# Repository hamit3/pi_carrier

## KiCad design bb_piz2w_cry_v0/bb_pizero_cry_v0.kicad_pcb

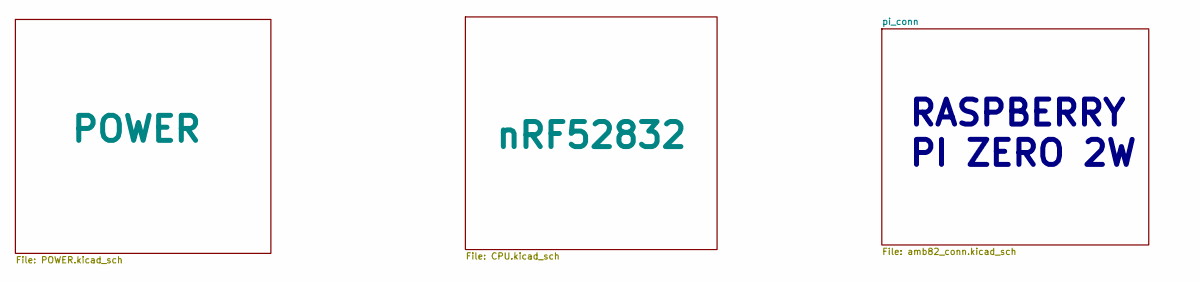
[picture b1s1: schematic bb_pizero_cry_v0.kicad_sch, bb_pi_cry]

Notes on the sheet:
RASPBERRY PI ZERO 2W

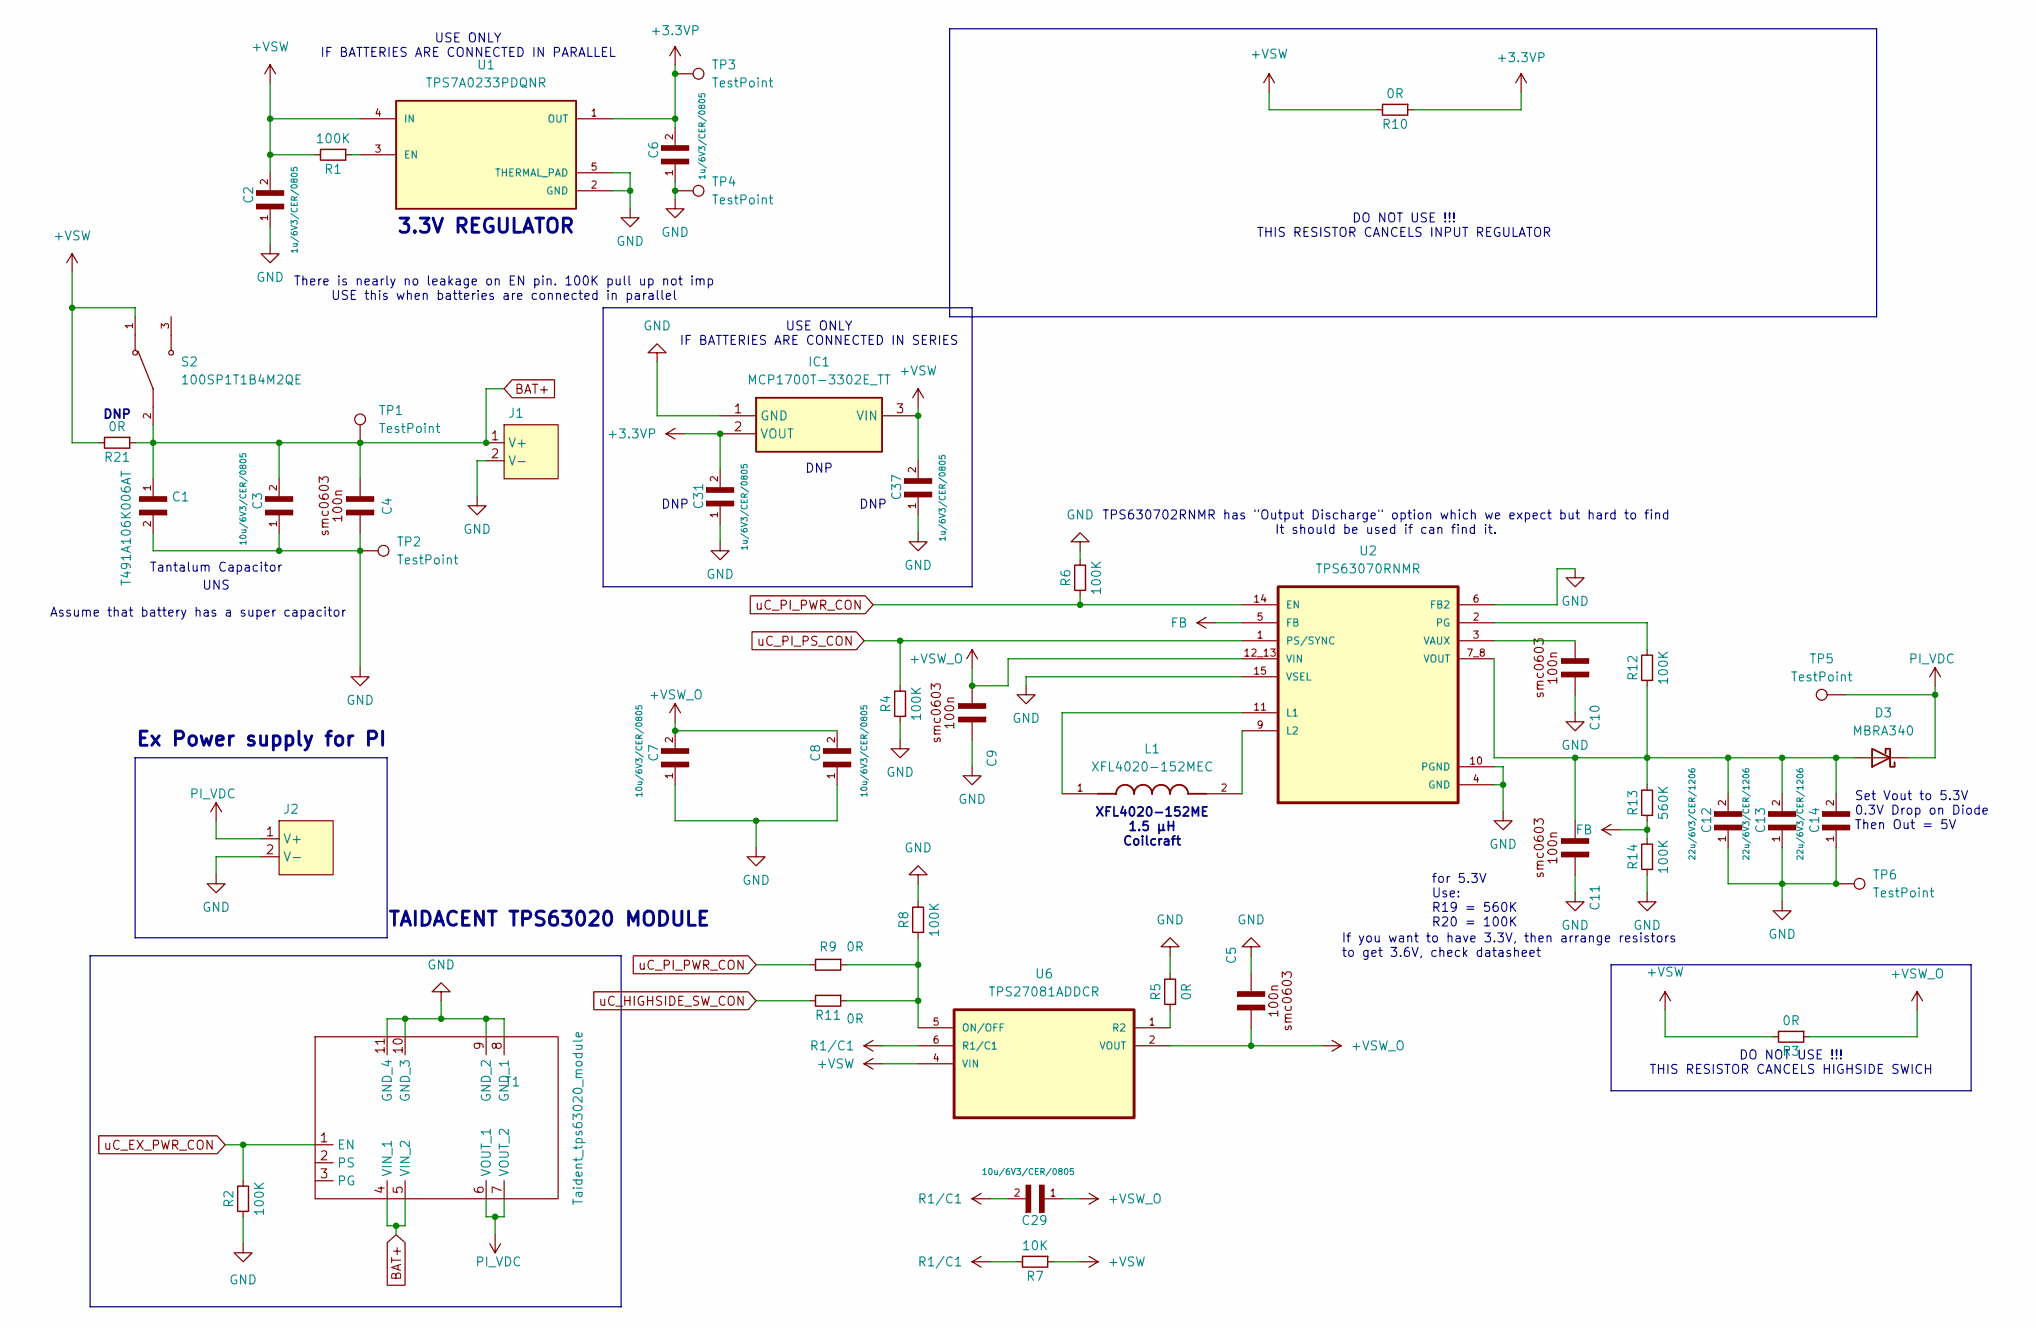
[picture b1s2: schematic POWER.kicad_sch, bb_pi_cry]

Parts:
C1: T491A106K006AT; CAPC3216X110N
C2, C6, C31, C37: 1u/6V3/CER/0805; CAPC2012X140N
C3, C7, C8, C29: 10u/6V3/CER/0805; CAPC2012X140N
C4, C5, C9, C10, C11: 100n; CAP_CL10_SAM
C12, C13, C14: 22u/6V3/CER/1206; C_1206_3216Metric_Pad1.33x1.80mm_HandSolder
D3: MBRA340; D_SMA; Part Number MBRA340T3GOSDKR-ND
IC1: MCP1700T-3302E_TT; SOT95P237X112-3N; Manufacturer_Part_Number MCP1700T-3302E/TT; Mouser Part Number 579-MCP1700T3302E/TT
J1: JST_PH_S2B-PH-K_1x02_P2.00mm_Horizontal
J2: JST_XH_B2B-XH-AM_1x02_P2.50mm_Vertical
L1: XFL4020-152MEC; IND_XFL4020-152MEC; PARTREV 11/02/18
R1, R4, R6, R8, R12, R14: 100K; RESC1508X55N
R2: 100K; R_1206_3216Metric_Pad1.30x1.75mm_HandSolder
R3, R10, R21: 0R; R_1206_3216Metric_Pad1.30x1.75mm_HandSolder
R5, R9, R11: 0R; RESC1508X55N
R7: 10K; RESC1508X55N
R13: 560K; RESC1508X55N
S2: 100SP1T1B4M2QE; SW_100SP1T1B4M2QE; PARTREV E
T1: Taident_tps63020_module; Taidacent_tps63020
TP1, TP2, TP3, TP4, TP5, TP6: TestPoint; TestPoint_Pad_2.0x2.0mm
U1: TPS7A0233PDQNR; SOT95P280X145-5N; PARTREV C
U2: TPS63070RNMR; VREG_TPS63070RNMR
U6: TPS27081ADDCR; SOT95P280X110-6N

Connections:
+3.3VP: C6.2, C31.2, IC1.2 (VOUT), R10.1, TP3.1, U1.1 (OUT); also elsewhere on the board
+VSW: C2.2, C37.2, IC1.3 (VIN), R1.2, R3.2, R7.1, R10.2, R21.2, S2.1, U1.4 (IN), U6.4 (VIN)
+VSW_O: C5.2, C7.2, C8.2, C9.2, C29.1, R3.1, U2.12_13 (VIN), U6.2 (VOUT), U6.3 (VOUT)
BAT+: C1.1, C3.2, C4.2, J1.1 (V+), R21.1, S2.2, T1.4 (VIN_1), T1.5 (VIN_2), TP1.1
FB: R13.1, R14.2, U2.5 (FB)
GND: C1.2, C2.1, C3.1, C4.1, C5.1, C6.1, C7.1, C8.1, C9.1, C10.1, C11.1, C12.1, C13.1, C14.1, C31.1, C37.1, IC1.1 (GND), J1.2 (V-), J2.2 (V-), R2.1, R4.1, R5.2, R6.2, R8.2, R14.1, T1.8 (GND_1), T1.9 (GND_2), T1.10 (GND_3), T1.11 (GND_4), TP2.1, TP4.1, TP6.1, U1.2 (GND), U1.5 (THERMAL_PAD), U2.4 (GND), U2.6 (FB2), U2.10 (PGND), U2.15 (VSEL); also elsewhere on the board
unnamed: C11.2, C12.2, C13.2, C14.2, D3.2 (A), R12.1, R13.2, U2.7_8 (VOUT)
unnamed: R1.1, U1.3 (EN)
unnamed: L1.1, U2.11 (L1)
unnamed: L1.2, U2.9 (L2)
unnamed: R12.2, U2.2 (PG)
unnamed: C10.2, U2.3 (VAUX)
unnamed: R8.1, R9.1, R11.1, U6.5 (ON/OFF)
unnamed: R5.1, U6.1 (R2)
PI_VDC: D3.1 (K), J2.1 (V+), T1.6 (VOUT_1), T1.7 (VOUT_2), TP5.1; also elsewhere on the board
R1/C1: C29.2, R7.2, U6.6 (R1/C1)
uC_EX_PWR_CON: R2.2, T1.1 (EN); also elsewhere on the board
uC_HIGHSIDE_SW_CON: R11.2; also elsewhere on the board
uC_PI_PS_CON: R4.2, U2.1 (PS/SYNC); also elsewhere on the board
uC_PI_PWR_CON: R6.1, R9.2, U2.14 (EN); also elsewhere on the board

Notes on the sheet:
TAIDACENT TPS63020 MODULE
UNS
Set Vout to 5.3V 0.3V Drop on Diode Then Out = 5V
DO NOT USE !!! THIS RESISTOR CANCELS INPUT REGULATOR
USE ONLY IF BATTERIES ARE CONNECTED IN SERIES
for 5.3V Use: R19 = 560K R20 = 100K
DNP
3.3V REGULATOR
Assume that battery has a super capacitor
There is nearly no leakage on EN pin. 100K pull up not imp USE this when batteries are connected in parallel
XFL4020-152ME 1.5 µH Coilcraft
USE ONLY IF BATTERIES ARE CONNECTED IN PARALLEL
DO NOT USE !!! THIS RESISTOR CANCELS HIGHSIDE SWICH
Tantalum Capacitor
TPS630702RNMR has "Output Discharge" option which we expect but hard to find It should be used if can find it.
Ex Power supply for PI
If you want to have 3.3V, then arrange resistors to get 3.6V, check datasheet

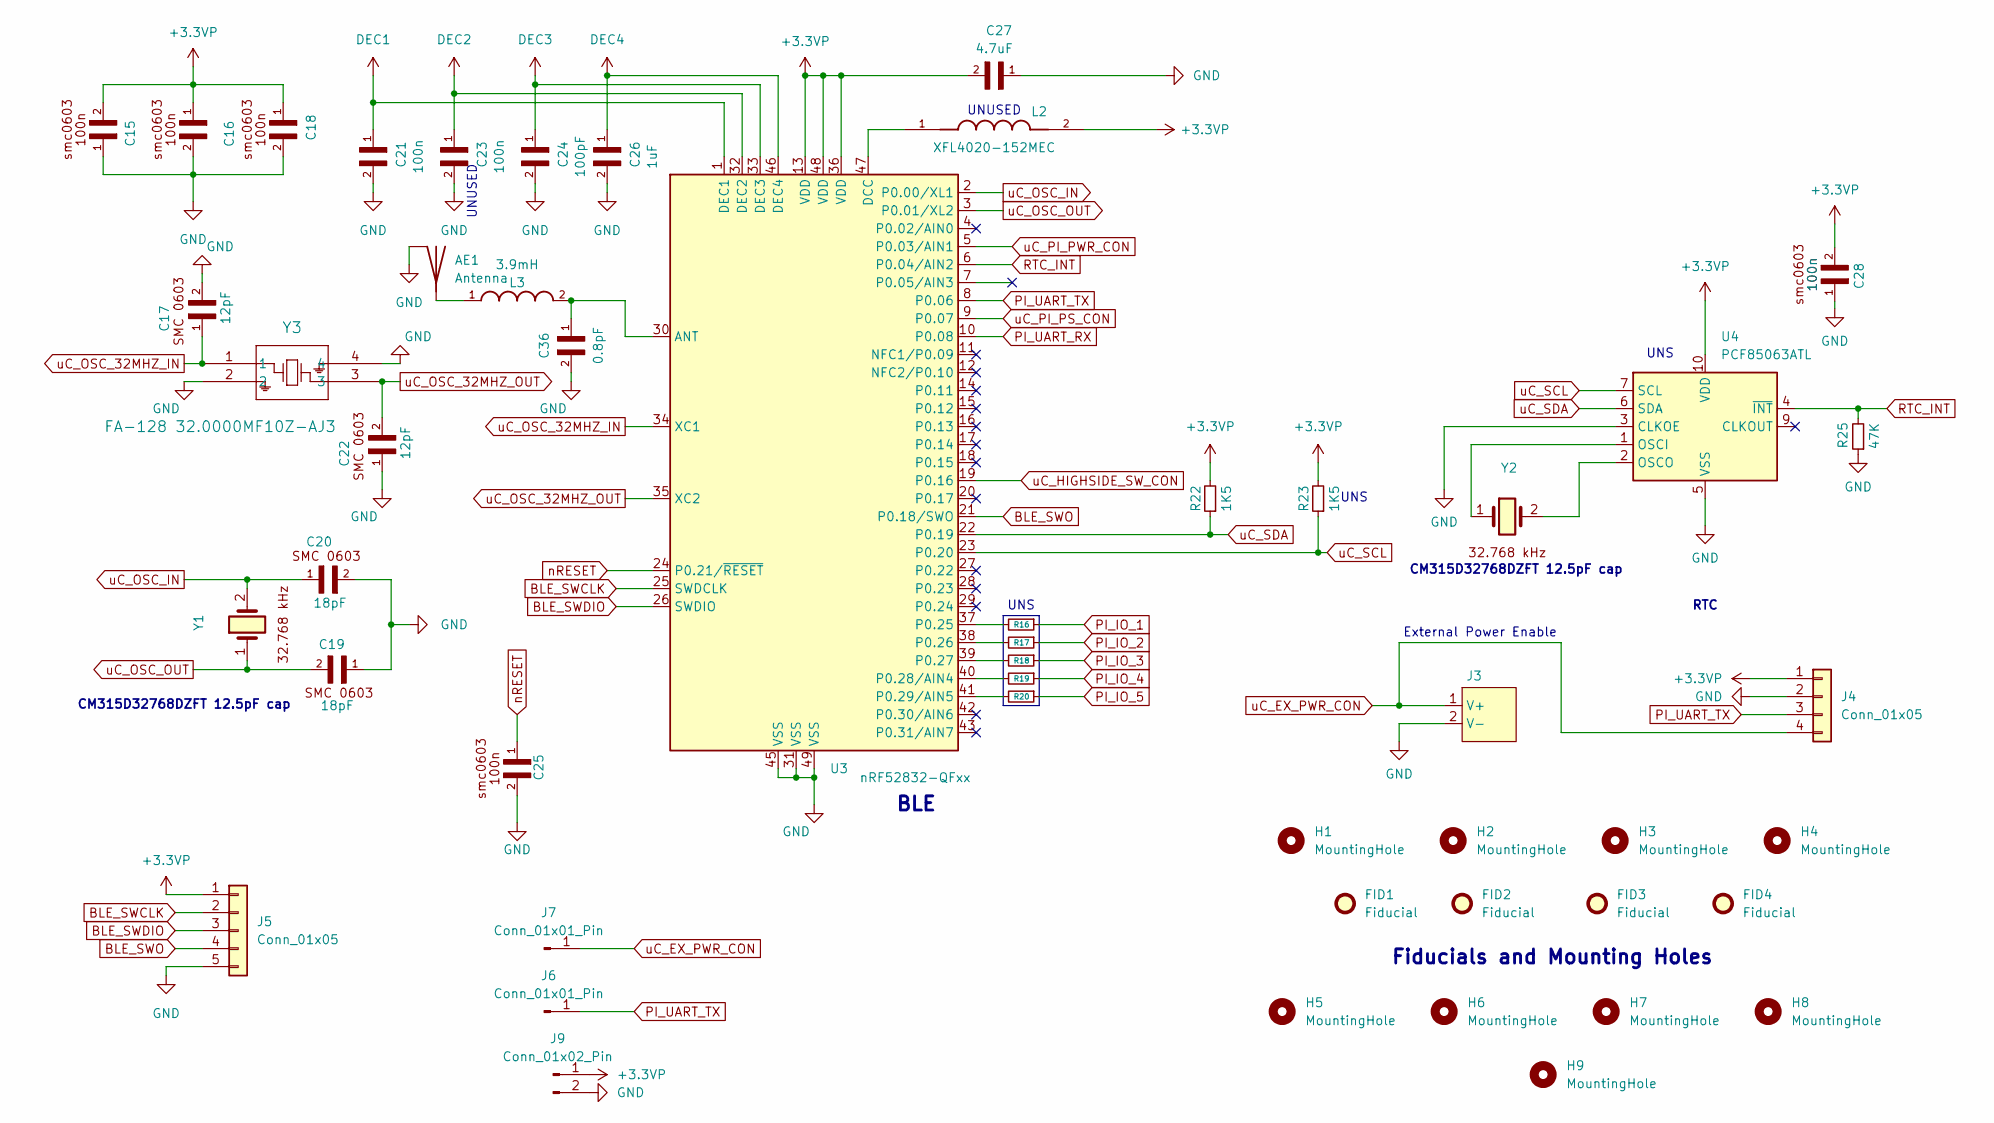
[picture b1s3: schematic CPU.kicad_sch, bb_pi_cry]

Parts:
AE1: Antenna; Texas_SWRA117D_2.4GHz_Right
C15, C16, C18, C21, C23, C25, C28: 100n; CAP_CL10_SAM
C17, C22: 12pF; CAPC1608X90N
C19, C20: 18pF; CAPC1608X90N
C24: 100pF; CAP_CL10_SAM
C26: 1uF; CAP_CL10_SAM
C27: 4.7uF; C_0201_0603Metric_Pad0.64x0.40mm_HandSolder
C36: 0.8pF; CAPC1005X55N
FID1, FID2, FID3, FID4: Fiducial; Fiducial_0.75mm_Mask2.25mm
H1, H2, H3, H4, H5, H6, H7, H8, H9: MountingHole; MountingHole_2.2mm_M2
J3: JST_XH_B2B-XH-AM_1x02_P2.50mm_Vertical
J4: Conn_01x05; PinHeader_1x04_P2.54mm_Vertical
J5: Conn_01x05; PinHeader_1x05_P2.54mm_Vertical
J6, J7: Conn_01x01_Pin; PinHeader_1x01_P2.54mm_Vertical
J9: Conn_01x02_Pin; PinHeader_1x02_P2.54mm_Vertical
L2: XFL4020-152MEC; IND_XFL4020-152MEC; PARTREV 11/02/18
L3: 3.9mH; INDC1005X55N
R16, R17, R18, R19, R20: 0R; RESC1508X55N
R22, R23: 1K5; RESC1508X55N
R25: 47K; RESC1508X55N
U3: nRF52832-QFxx; QFN-48-1EP_6x6mm_P0.4mm_EP4.6x4.6mm
U4: PCF85063ATL; DFN-10-1EP_2.6x2.6mm_P0.5mm_EP1.3x2.2mm
Y1, Y2: XTAL_CM315D32768DZFT
Y3: FA-128 32.0000MF10Z-AJ3; FA-128_EPS

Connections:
+3.3VP: C15.2, C16.1, C18.1, C27.2, C28.2, J4.1, J5.1, J9.1, L2.2, R22.2, R23.2, U3.13 (VDD), U3.36 (VDD), U3.48 (VDD), U4.10 (VDD); also elsewhere on the board
BLE_SWCLK: J5.2, U3.25 (SWDCLK)
BLE_SWDIO: J5.3, U3.26 (SWDIO)
BLE_SWO: J5.4, U3.21 (P0.18/SWO)
DEC1: C21.1, U3.1 (DEC1)
DEC2: C23.1, U3.32 (DEC2)
DEC3: C24.1, U3.33 (DEC3)
DEC4: C26.1, U3.46 (DEC4)
GND: AE1.2 (GND_Ref), C15.1, C16.2, C17.2, C18.2, C19.1, C20.2, C21.2, C22.1, C23.2, C24.2, C25.2, C26.2, C27.1, C28.1, C36.2, J3.2 (V-), J4.2, J5.5, J9.2, R25.1, U3.31 (VSS), U3.45 (VSS), U3.49 (VSS), U4.3 (CLKOE), U4.5 (VSS), Y3.2, Y3.4; also elsewhere on the board
unnamed: AE1.1 (A), L3.1
unnamed: C36.1, L3.2, U3.30 (ANT)
unnamed: L2.1, U3.47 (DCC)
unnamed: R16.2, U3.37 (P0.25)
unnamed: R17.2, U3.38 (P0.26)
unnamed: R18.2, U3.39 (P0.27)
unnamed: R19.2, U3.40 (P0.28/AIN4)
unnamed: R20.2, U3.41 (P0.29/AIN5)
unnamed: U4.1 (OSCI), Y2.1
unnamed: U4.2 (OSCO), Y2.2
PI_IO_1: R16.1; also elsewhere on the board
PI_IO_2: R17.1; also elsewhere on the board
PI_IO_3: R18.1; also elsewhere on the board
PI_IO_4: R19.1; also elsewhere on the board
PI_IO_5: R20.1; also elsewhere on the board
PI_UART_RX: U3.10 (P0.08); also elsewhere on the board
PI_UART_TX: J4.3, J6.1, U3.8 (P0.06); also elsewhere on the board
RTC_INT: R25.2, U3.6 (P0.04/AIN2), U4.4 (~INT)
nRESET: C25.1, U3.24 (P0.21/~RESET)
uC_EX_PWR_CON: J3.1 (V+), J4.4, J7.1; also elsewhere on the board
uC_HIGHSIDE_SW_CON: U3.19 (P0.16); also elsewhere on the board
uC_OSC_32MHZ_IN: C17.1, U3.34 (XC1), Y3.1
uC_OSC_32MHZ_OUT: C22.2, U3.35 (XC2), Y3.3
uC_OSC_IN: C20.1, U3.2 (P0.00/XL1), Y1.2
uC_OSC_OUT: C19.2, U3.3 (P0.01/XL2), Y1.1
uC_PI_PS_CON: U3.9 (P0.07); also elsewhere on the board
uC_PI_PWR_CON: U3.5 (P0.03/AIN1); also elsewhere on the board
uC_SCL: R23.1, U3.23 (P0.20), U4.7 (SCL)
uC_SDA: R22.1, U3.22 (P0.19), U4.6 (SDA)

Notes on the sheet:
RTC
UNS
UNUSED
CM315D32768DZFT 12.5pF cap
Fiducials and Mounting Holes
BLE
External Power Enable

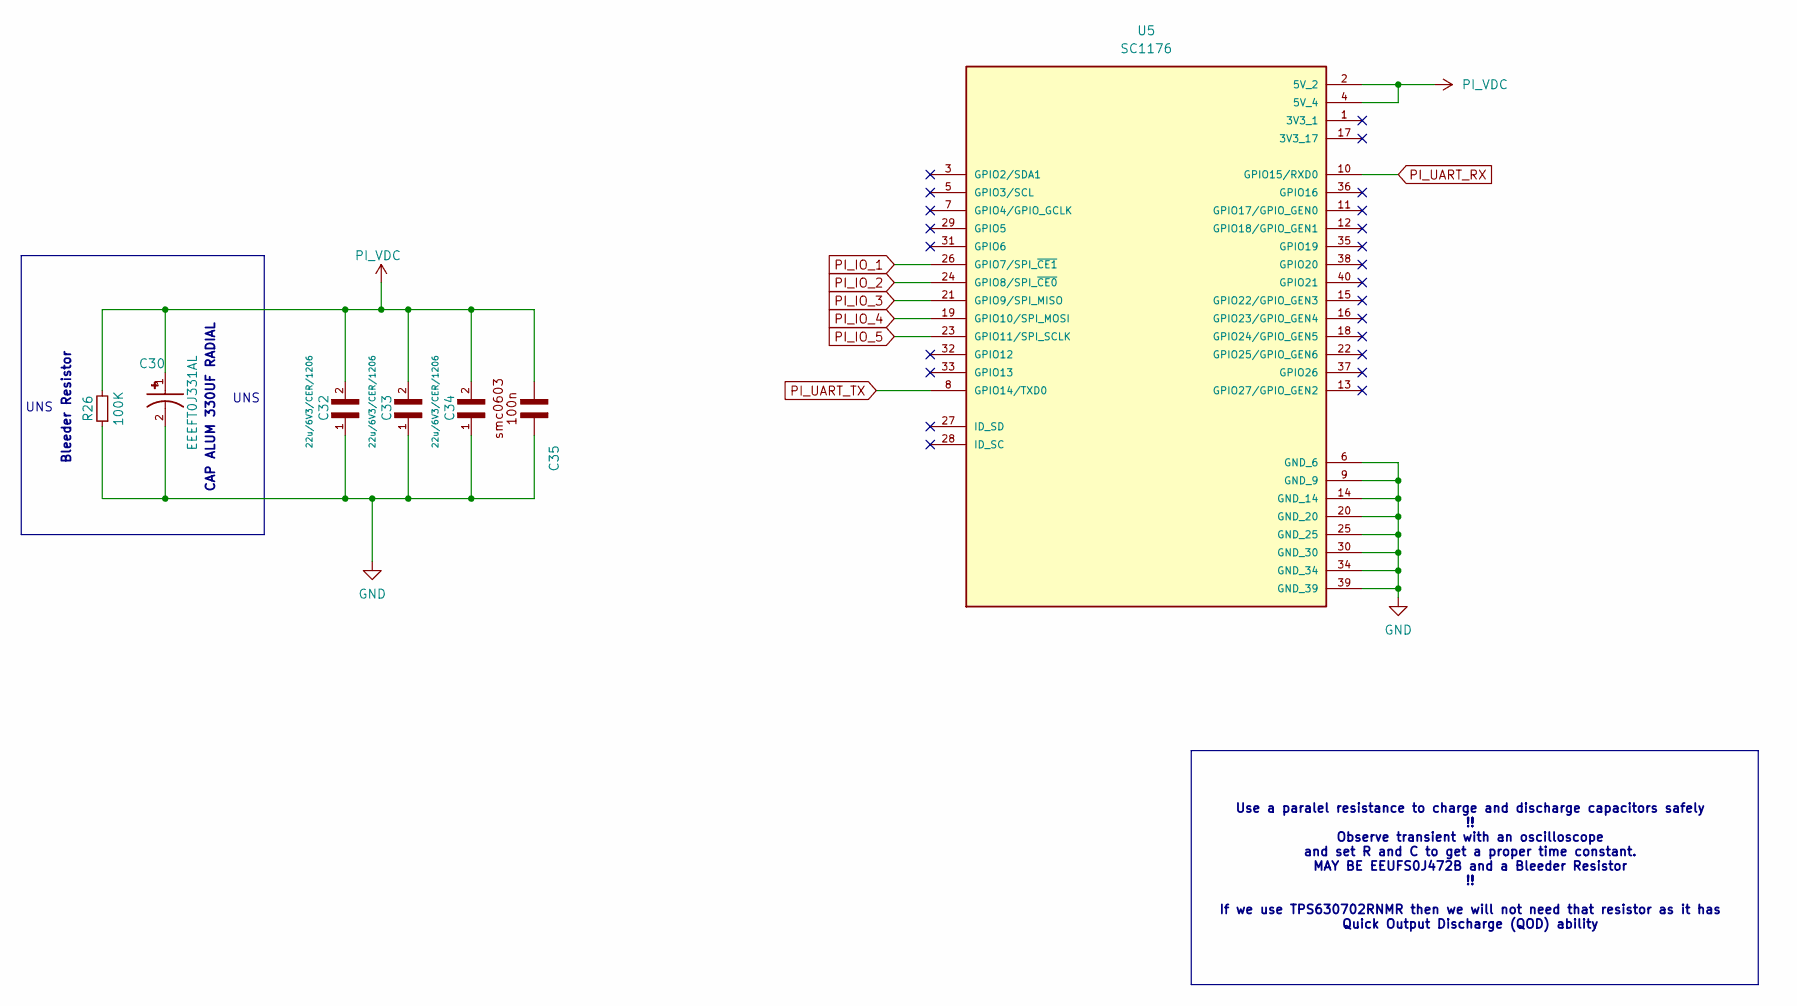
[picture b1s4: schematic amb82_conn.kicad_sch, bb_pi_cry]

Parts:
C30: EEEFT0J331AL; CAP_EEEFT0J331AL; PARTREV 10-Oct-19
C32, C33, C34: 22u/6V3/CER/1206; C_1206_3216Metric_Pad1.33x1.80mm_HandSolder
C35: 100n; CAP_CL10_SAM
R26: 100K; R_1206_3216Metric_Pad1.30x1.75mm_HandSolder
U5: SC1176; Raspberry_Pi_Zero_Socketed_THT_FaceDown_MountingHoles; PARTREV April 2024

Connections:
GND: C30.2, C32.1, C33.1, C34.1, C35.1, R26.1, U5.6 (GND_6), U5.9 (GND_9), U5.14 (GND_14), U5.20 (GND_20), U5.25 (GND_25), U5.30 (GND_30), U5.34 (GND_34), U5.39 (GND_39); also elsewhere on the board
PI_IO_1: U5.26 (GPIO7/SPI_~CE1); also elsewhere on the board
PI_IO_2: U5.24 (GPIO8/SPI_~CE0); also elsewhere on the board
PI_IO_3: U5.21 (GPIO9/SPI_MISO); also elsewhere on the board
PI_IO_4: U5.19 (GPIO10/SPI_MOSI); also elsewhere on the board
PI_IO_5: U5.23 (GPIO11/SPI_SCLK); also elsewhere on the board
PI_UART_RX: U5.10 (GPIO15/RXD0); also elsewhere on the board
PI_UART_TX: U5.8 (GPIO14/TXD0); also elsewhere on the board
PI_VDC: C30.1, C32.2, C33.2, C34.2, C35.2, R26.2, U5.2 (5V_2), U5.4 (5V_4); also elsewhere on the board

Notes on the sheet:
CAP ALUM 330UF RADIAL
Use a paralel resistance to charge and discharge capacitors safely !! Observe transient with an oscilloscope and set R and C to get a proper time constant. MAY BE EEUFS0J472B and a Bleeder Resistor !! If we use TPS630702RNMR then we will not need that resistor as it has Quick Output Discharge (QOD)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
UNS
Bleeder Resistor

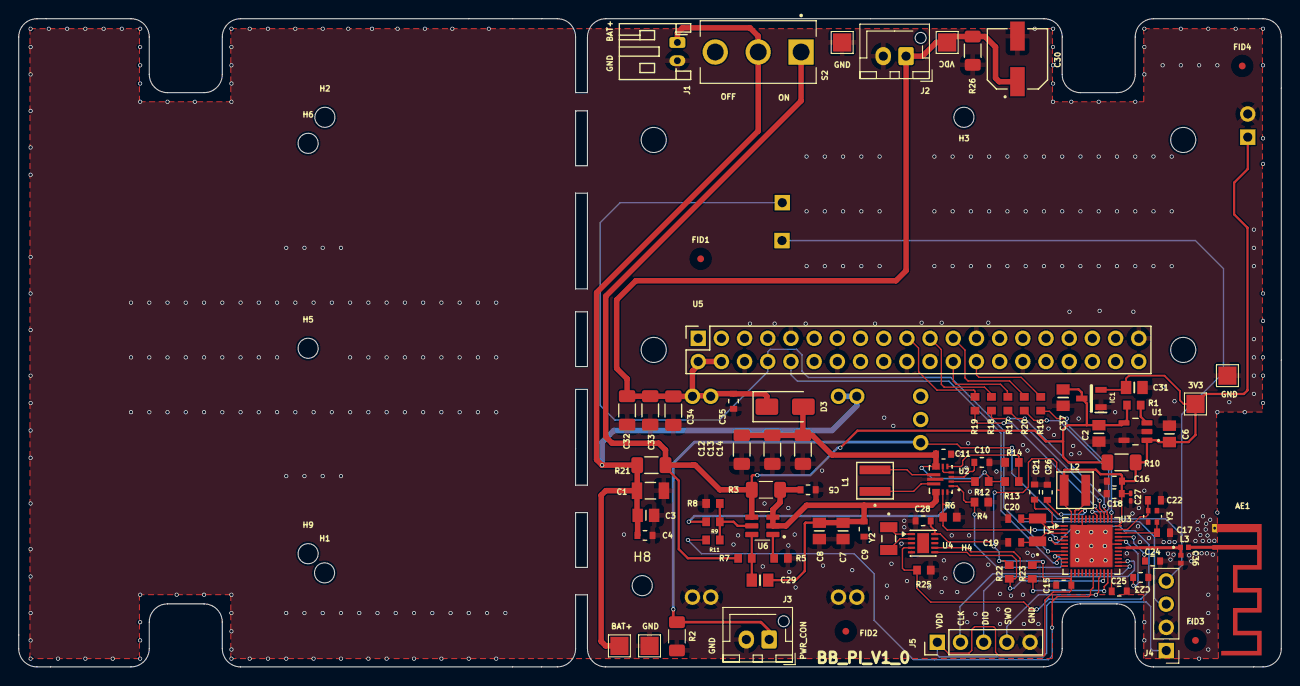
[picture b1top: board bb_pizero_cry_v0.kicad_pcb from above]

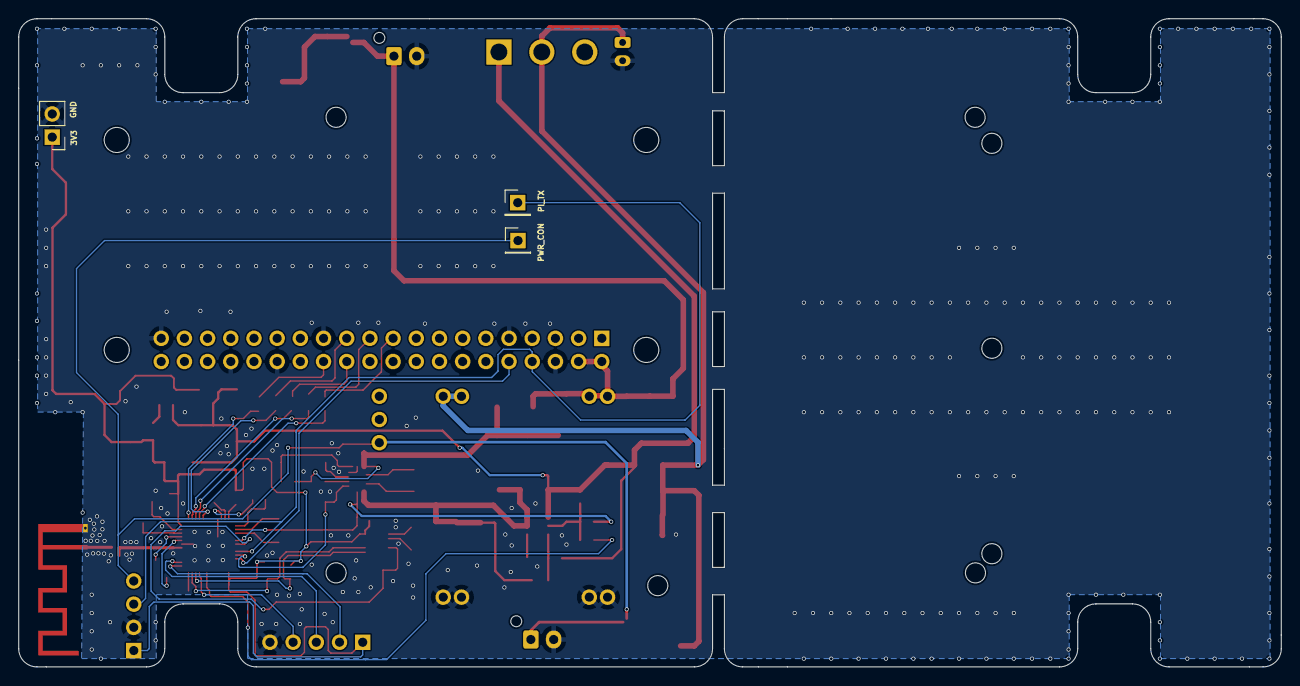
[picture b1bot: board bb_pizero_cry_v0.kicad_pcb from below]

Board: 2 copper layers, 138.3 x 71.0 mm, 104 parts (3 on the bottom side), 52 nets.
